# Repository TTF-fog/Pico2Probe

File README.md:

# a RP2354-based debugprobe

An updated version of the original [debugprobe](https://www.raspberrypi.com/documentation/microcontrollers/debug-probe.html) with the following changes - 
- Based on the RP2354A
- USB-C (i just really hate micro-b)
- a configurable addressable RGB led

### Build

SWD, uart works

# Why did i make this?

1. Does one need to justify the act of creation? (or, in other words, why not?) (please do not take that out of context)
2. I had no way of debugging except plain UART (which is annoying), so i wanted something that would let me use an actual debugger
3. Wanted to make something using the RP2354A

# Setting Up
1. the board will already have a bootloader on it, plug it in and mount the drive
2. do git submodule sync and git submodule update --init --recursive
3. cd into debugprobe directory and
4. cmake -B build-pico2probe -DPICO_BOARD=pico2probe && make -C build-pico2probe -j$(nproc)
5. drag the pico2probe.uf2 file into the flash drive

# Firmware Modifications
- opening and closing the port at 1200 baud automatically puts the device into BOOTSEL mode
- board support files for the pico2probe
# Usage
for UART RX/TX, 
```shell
screen /dev/ttyACMx
```
for using SWD, eg. flashing a rp2040 do:
```shell
sudo openocd -f interface/cmsis-dap.cfg -f target/rp2040.cfg -c "adapter speed 5000" -c "program blink.elf verify reset exit"
```
# (Sub)Links
- [BOM](PCB/production_files/BOM.csv)
- [Design Files](PCB/Design%20Files/)
- [Schematic PDF](PCB/Design%20Files/schem.pdf/Pico2Probe.pdf)
- [Zine](zine.pdf)
- [Gerbers](PCB/production_files/GERBER-Pico2Probe.zip)

# Images

# Current Issues
- Silkscreen text is difficult to read due to small size
- buffer on UART is on wrong pin
- uses green and red leds, not yellow and red leds
- solder jumpers are difficult to use reliably
- bootsel does not work due to resistor configuuration issues

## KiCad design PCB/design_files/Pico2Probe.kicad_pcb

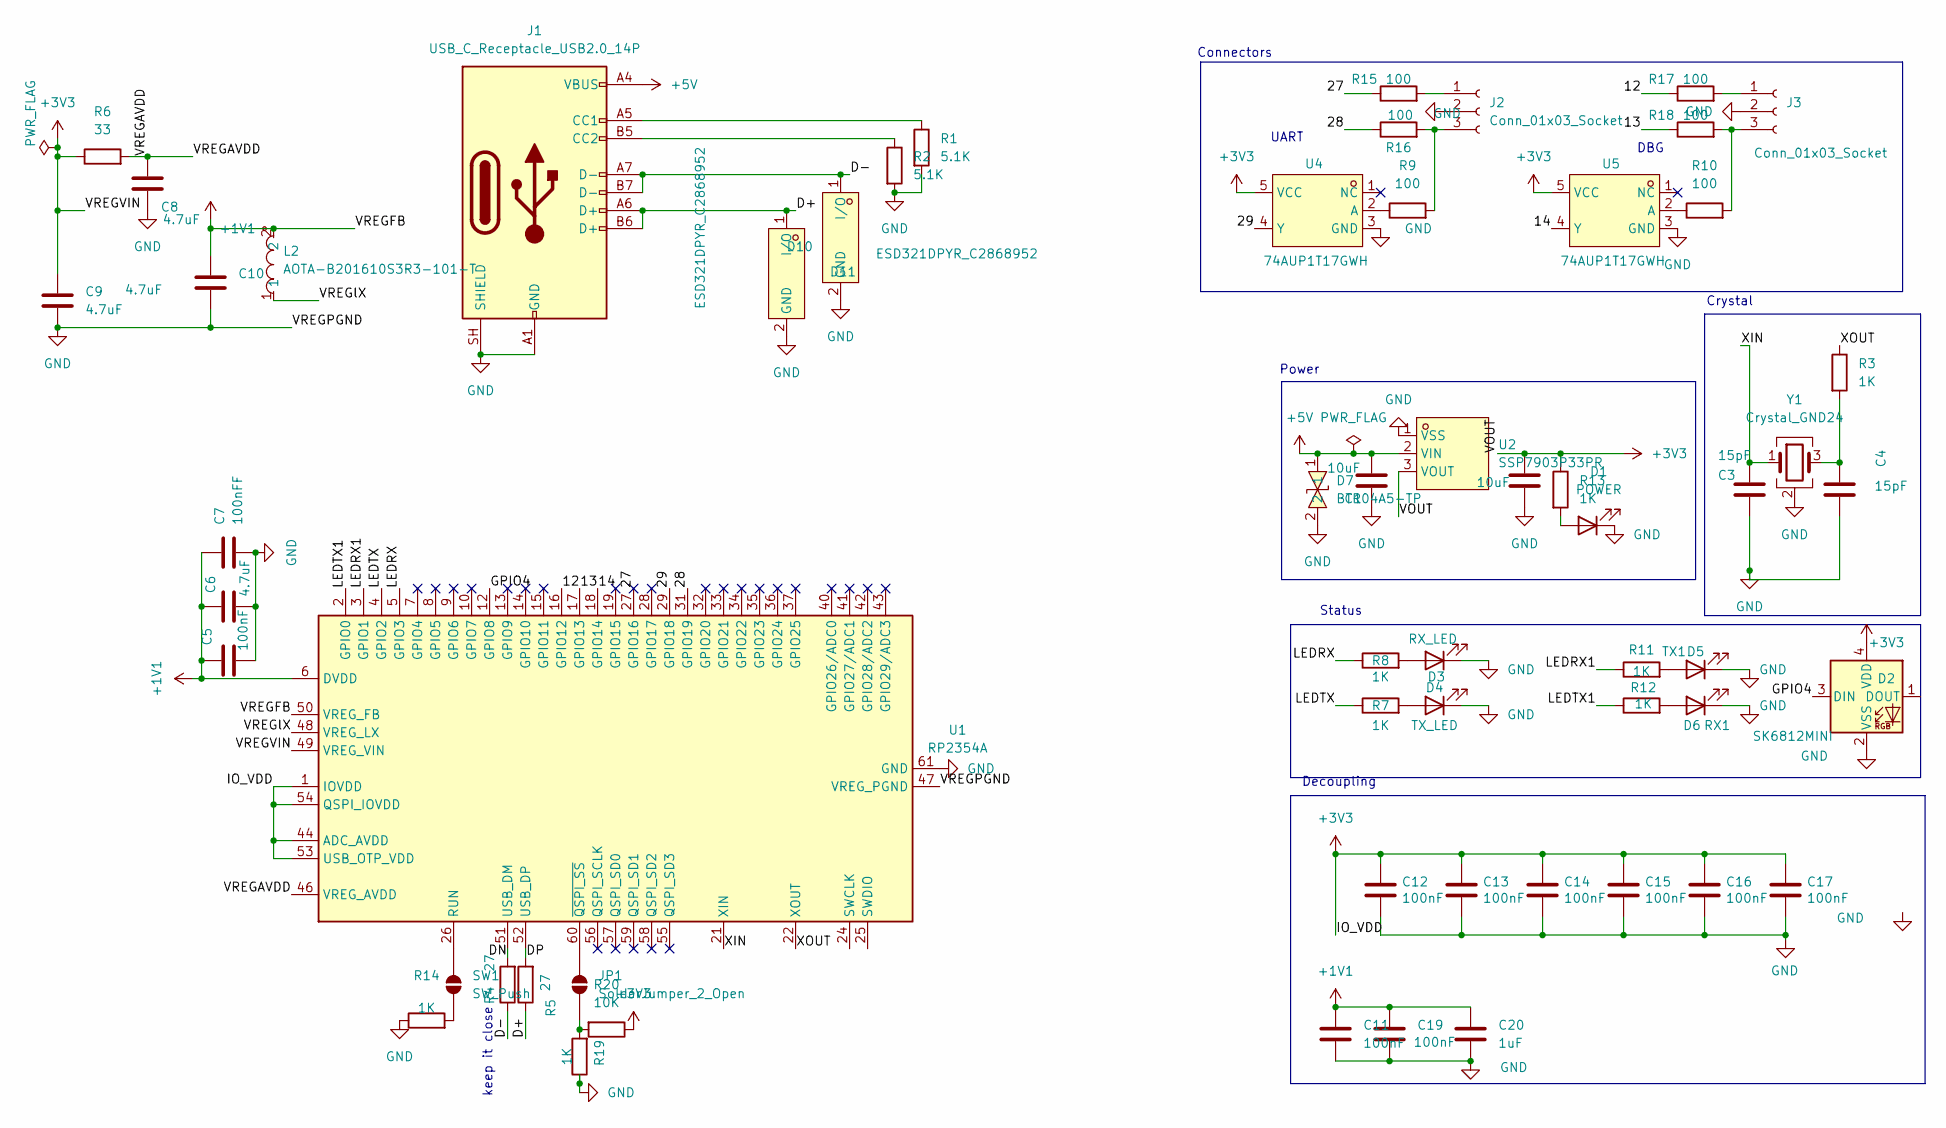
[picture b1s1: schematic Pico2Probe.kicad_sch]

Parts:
C1, C2: 10uF; C_0402_1005Metric
C3, C4: 15pF; C_0402_1005Metric
C5, C11, C12, C13, C14, C15, C16, C17, C19: 100nF; C_0402_1005Metric
C6, C8, C9, C10: 4.7uF; C_0402_1005Metric
C7: 100nFF; C_0402_1005Metric
C20: 1uF; C_0402_1005Metric
D1: POWER; LED_0402_1005Metric
D2: SK6812MINI; LED_SK6812_EC15_1.5x1.5mm
D3: RX_LED; LED_0402_1005Metric
D4: TX_LED; LED_0402_1005Metric
D5: TX1; LED_0402_1005Metric
D6: RX1; LED_0402_1005Metric
D7: BTR04A5-TP; D0402-BI; MPN BTR04A5-TP; LCSC Part C42406343
D10, D11: ESD321DPYR_C2868952; X1SON-2_L1.0-W0.6-P0.65-RD-1; MPN ESD321DPYR; LCSC Part C2868952
J1: USB_C_Receptacle_USB2.0_14P; USB_C_Receptacle_HRO_TYPE-C-31-M-12
J2, J3: Conn_01x03_Socket; JST_SH_BM03B-SRSS-TB_1x03-1MP_P1.00mm_Vertical
JP1: SolderJumper_2_Open; SolderJumper-2_P1.3mm_Open_RoundedPad1.0x1.5mm
L2: AOTA-B201610S3R3-101-T; IND-SMD_L2.0-W1.6_AOTA-B201610S3R3-101-T; MPN AOTA-B201610S3R3-101-T; LCSC Part C42411119
R1, R2: 5.1K; R_0402_1005Metric
R3, R7, R8, R11, R12, R13, R14, R19: 1K; R_0402_1005Metric
R4, R5: 27; R_0402_1005Metric
R6: 33; R_0402_1005Metric
R9, R10, R15, R16, R17, R18: 100; R_0402_1005Metric
R20: 10K; R_0402_1005Metric
SW1: SW_Push; SolderJumper-2_P1.3mm_Open_RoundedPad1.0x1.5mm
U1: RP2354A; QFN-60-1EP_7x7mm_P0.4mm_EP3.4x3.4mm
U2: SSP7903P33PR; SOT-89-3_L4.5-W2.5-P1.50-LS4.1-BR; MPN SSP7903P33PR; LCSC Part C2965586
U4, U5: 74AUP1T17GWH; TSSOP-5_L2.1-W1.3-P0.65-LS2.2-BR; MPN 74AUP1T17GWH
Y1: Crystal_GND24; Crystal_SMD_3225-4Pin_3.2x2.5mm

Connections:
+1V1: C5.1, C6.1, C7.1, C10.1, C11.1, C19.1, C20.1, L2.2, U1.6 (DVDD), U1.23 (DVDD), U1.39 (DVDD), U1.50 (VREG_FB)
+3V3: C2.1, C9.1, C12.1, C13.1, C14.1, C15.1, C16.1, C17.1, D2.4 (VDD), R6.1, R13.1, R20.1, U1.1 (IOVDD), U1.11 (IOVDD), U1.20 (IOVDD), U1.30 (IOVDD), U1.38 (IOVDD), U1.44 (ADC_AVDD), U1.45 (IOVDD), U1.49 (VREG_VIN), U1.53 (USB_OTP_VDD), U1.54 (QSPI_IOVDD), U2.3 (VOUT), U4.5 (VCC), U5.5 (VCC)
+5V: C1.1, D7.1, J1.A4 (VBUS), J1.A9 (VBUS), J1.B4 (VBUS), J1.B9 (VBUS), U2.2 (VIN)
/12: R17.1, U1.16 (GPIO12)
/13: R18.1, U1.17 (GPIO13)
/14: U1.18 (GPIO14), U5.4 (Y)
/27: R15.1, U1.27 (GPIO16)
/28: R16.1, U1.31 (GPIO19)
/29: U1.29 (GPIO18), U4.4 (Y)
/D+: D11.1 (I/O), J1.A6 (D+), J1.B6 (D+), R5.1
/D-: D10.1 (I/O), J1.A7 (D-), J1.B7 (D-), R4.1
/DN: R4.2, U1.51 (USB_DM)
/DP: R5.2, U1.52 (USB_DP)
/GPIO4: D2.3 (DIN), U1.12 (GPIO8)
/LEDRX: R8.1, U1.5 (GPIO3)
/LEDRX1: R11.1, U1.3 (GPIO1)
/LEDTX: R7.1, U1.4 (GPIO2)
/LEDTX1: R12.1, U1.2 (GPIO0)
/VREGAVDD: C8.1, R6.2, U1.46 (VREG_AVDD)
/VREGlX: L2.1, U1.48 (VREG_LX)
/XIN: C3.1, U1.21 (XIN), Y1.1
/XOUT: R3.1, U1.22 (XOUT)
GND: C1.2, C2.2, C3.2, C4.2, C5.2, C6.2, C7.2, C8.2, C9.2, C10.2, C11.2, C12.2, C13.2, C14.2, C15.2, C16.2, C17.2, C19.2, C20.2, D1.1 (K), D2.2 (VSS), D3.1 (K), D4.1 (K), D5.1 (K), D6.1 (K), D7.2, D10.2 (GND), D11.2 (GND), J1.A1 (GND), J1.A12 (GND), J1.B1 (GND), J1.B12 (GND), J1.SH (SHIELD), J2.2, J3.2, R1.2, R2.2, R14.1, R19.1, U1.47 (VREG_PGND), U1.61 (GND), U2.1 (VSS), U4.3 (GND), U5.3 (GND), Y1.2 (G), Y1.4 (G); also elsewhere on the board
unnamed: C4.1, R3.2, Y1.3
unnamed 24: D1.2 (A), R13.2; also elsewhere on the board
unnamed: D3.2 (A), R8.2
unnamed: D4.2 (A), R7.2
unnamed: D5.2 (A), R11.2
unnamed: D6.2 (A), R12.2
unnamed: J1.A5 (CC1), R1.1
unnamed: J1.B5 (CC2), R2.1
unnamed: J2.1, R15.2
unnamed: J2.3, R9.2, R16.2
unnamed: J3.1, R17.2
unnamed: J3.3, R10.2, R18.2
unnamed: JP1.1 (A), R19.2, R20.2
unnamed: JP1.2 (B), U1.60 (~QSPI_SS)
unnamed: R14.2, SW1.1 (A)
unnamed: SW1.2 (B), U1.26 (RUN)
unnamed: R9.1, U4.2 (A)
unnamed: R10.1, U5.2 (A)

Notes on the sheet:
UART
keep it close
Connectors
Crystal
Decoupling
DBG
Status
Power

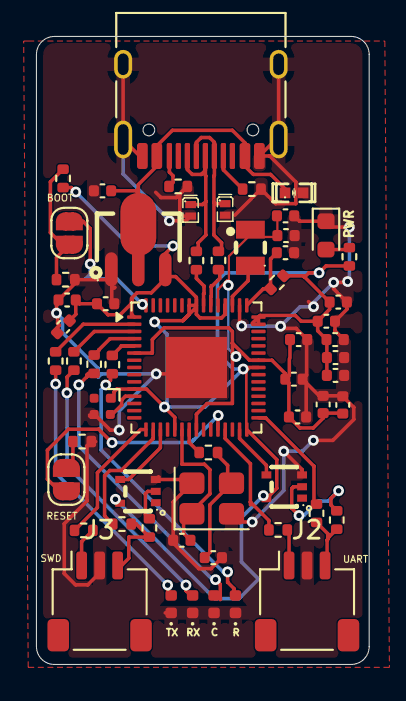
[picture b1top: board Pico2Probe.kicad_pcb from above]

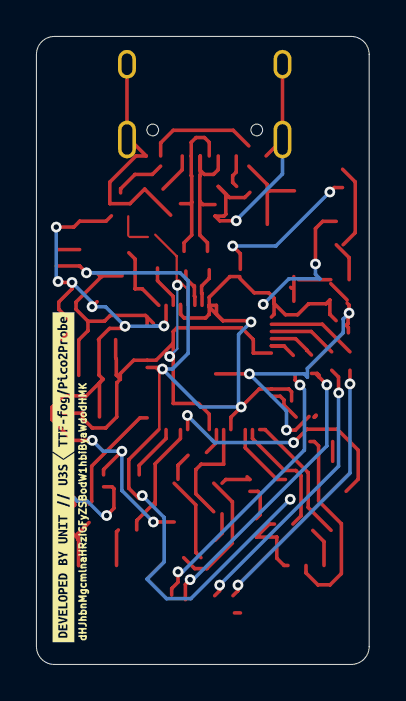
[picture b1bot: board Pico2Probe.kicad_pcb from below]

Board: 2 copper layers, 18.5 x 34.9 mm, 61 parts (2 on the bottom side), 41 nets.

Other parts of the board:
PWR: POWER; LED_0603_1608Metric
kibuzzard-6A06DE47: G***; kibuzzard-6A06DE47
kibuzzard-6A06DEAD: G***; kibuzzard-6A06DEAD

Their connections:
GND: PWR.1 (K); also elsewhere on the board
unnamed 24: PWR.2 (A); also elsewhere on the board

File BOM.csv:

Comment,Designator,Footprint,LCSC,Quantity,LCSC_Link,Original Cost,LCSC Unit Price (USD),BOM Qty Cost (USD),MOQ,MOQ Order Qty,MOQ Order Cost (USD),Stock/Pricing Status,Source URL
100,"R10,R15,R16,R17,R18,R9",R_0402_1005Metric,C25076,6,https://lcsc.com/product/C25076.html,$0.03,0.001,0.006,100,100,0.1,In stock,https://www.lcsc.com/product-detail/C25076.html
100nF,"C11,C12,C13,C14,C15,C16,C17,C19,C5",C_0402_1005Metric,C1525,9,https://lcsc.com/product/C1525.html,$0.08,0.0015,0.0135,100,100,0.15,In stock,https://www.lcsc.com/product-detail/C1525.html
100nFF,C7,C_0402_1005Metric,C1525,1,https://lcsc.com/product/C1525.html,$0.13,0.0015,0.0015,100,100,0.15,In stock,https://www.lcsc.com/product-detail/C1525.html
10uF,"C1,C2",C_0402_1005Metric,C15525,2,https://lcsc.com/product/C15525.html,$0.07,0.007,0.014,100,100,0.7,In stock,https://www.lcsc.com/product-detail/C15525.html
15pF,"C3,C4",C_0402_1005Metric,C1548,2,https://lcsc.com/product/C1548.html,,0.0012,0.0024,100,100,0.12,In stock,https://www.lcsc.com/product-detail/C1548.html
1K,"R11,R12,R13,R14,R19,R3,R7,R8",R_0402_1005Metric,C11702,8,https://lcsc.com/product/C11702.html,,0.0011,0.0088,100,100,0.11,Out of stock,https://www.lcsc.com/product-detail/C11702.html
1uF,C20,C_0402_1005Metric,C52923,1,https://lcsc.com/product/C52923.html,,0.004,0.004,100,100,0.4,In stock,https://www.lcsc.com/product-detail/C52923.html
27,"R4,R5",R_0402_1005Metric,C138021,2,https://lcsc.com/product/C138021.html,,0.0008,0.0016,100,100,0.08,In stock,https://www.lcsc.com/product-detail/C138021.html
3.3u,L1,L_0402_1005Metric,C48946153,1,https://lcsc.com/product/C48946153.html,,0.0425,0.0425,10,10,0.425,In stock,https://www.lcsc.com/product-image/C48946153.html
33,R6,R_0402_1005Metric,C25105,1,https://lcsc.com/product/C25105.html,,0.0009,0.0009,100,100,0.09,In stock,https://www.lcsc.com/product-detail/C25105.html
4.7uF,"C10,C6,C8,C9",C_0402_1005Metric,C23733,4,https://lcsc.com/product/C23733.html,,0.0063,0.0252,50,50,0.315,In stock,https://www.lcsc.com/product-detail/C23733.html
5.1K,"R1,R2",R_0402_1005Metric,C25905,2,https://lcsc.com/product/C25905.html,,0.0009,0.0018,100,100,0.09,In stock,https://www.lcsc.com/product-detail/C25905.html
BTR04A5-TP,D7,D0402-BI,C42406343,1,https://lcsc.com/product/C42406343.html,,0.0252,0.0252,20,20,0.504,In stock,https://www.lcsc.com/product-detail/C42406343.html
Conn_01x03_Socket,"J2,J3",JST_ACH_BM03B-ACHSS-GAN-ETF_1x03-1MP_P1.20mm_Vertical,C53368148,2,https://lcsc.com/product/C53368148.html,,,,1,1,0.38,In stock,https://www.lcsc.com/product-detail/C53368148.html
Crystal_GND24,Y1,Crystal_SMD_3225-4Pin_3.2x2.5mm,C20625731,1,https://lcsc.com/product/C20625731.html,,0.2947,0.2947,5,5,1.4735,In stock,https://www.lcsc.com/product-detail/C20625731.html
ESD321DPYR_C2868952,"D10,D11",X1SON-2_L1.0-W0.6-P0.65-RD-1,C2868952,2,https://lcsc.com/product/C2868952.html,1.81,0.2751,0.5502,5,5,1.3755,In stock,https://www.lcsc.com/product-detail/C2868952.html
RP2354A,U1,QFN-60-1EP_7x7mm_P0.4mm_EP3.4x3.4mm,C41378174,1,https://lcsc.com/product/C41378174.html,3,1.4926,1.4926,1,1,1.4926,Out of stock,https://www.lcsc.com/product-detail/C41378174.html
RX1,D6,LED_0402_1005Metric,C598352,1,https://lcsc.com/product/C598352.html,0.447,0.3451,0.3451,1,1,0.3451,In stock,https://www.lcsc.com/product-detail/C598352.html
RX_LED,D3,LED_0402_1005Metric,C598352,1,https://lcsc.com/product/C598352.html,0.447,0.3451,0.3451,1,1,0.3451,In stock,https://www.lcsc.com/product-detail/C598352.html
TX1,D5,LED_0402_1005Metric,C598352,1,https://lcsc.com/product/C598352.html,0.447,0.3451,0.3451,1,1,0.3451,In stock,https://www.lcsc.com/product-detail/C598352.html
TX_LED,D4,LED_0402_1005Metric,C598352,1,https://lcsc.com/product/C598352.html,0.447,0.3451,0.3451,1,1,0.3451,In stock,https://www.lcsc.com/product-detail/C598352.html
USB_C_Receptacle_USB2.0_14P,J1,USB_C_Receptacle_HRO_TYPE-C-31-M-12,C165948,1,https://lcsc.com/product/C165948.html,,0.1709,0.1709,5,5,0.8545,In stock,https://www.lcsc.com/product-detail/C165948.html
MCP1700x-330xxMB,U6,SOT-89-3,C511277,1,https://lcsc.com/product/C511277,0.8,0.803,0.803,1,1,0.803,In stock,https://www.lcsc.com/product-detail/C511277.html
POWER,D1,LED_0402_1005Metric,C598352,1,https://lcsc.com/product/C598352.html,,0.3451,0.3451,1,1,0.3451,In stock,https://www.lcsc.com/product-detail/C598352.html
74AUP1T17GWH,U4,TSSOP-5_L2.1-W1.3-P0.65-LS2.2-BR,C545951,1,https://lcsc.com/product/C545951.html,$2.72,0.2797,0.2797,5,5,1.3985,In stock,https://www.lcsc.com/product-detail/C545951.html
SK6812MINI,D2,LED_SK6812_EC15_1.5x1.5mm,C2890035,1,https://lcsc.com/product/C2890035.html,,0.093,0.093,5,5,0.465,In stock,https://www.lcsc.com/product-detail/C2890035.html
74AUP1T17GWH,U5,TSSOP-5_L2.1-W1.3-P0.65-LS2.2-BR,C545951,1,https://lcsc.com/product/C545951.html,$2.72,0.2797,0.2797,5,5,1.3985,In stock,https://www.lcsc.com/product-detail/C545951.html
,,,,,,,Totals,5.8367,,,14.6006,,

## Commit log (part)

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2026-05-14 pcb 1
2026-05-17 update organization + pcb
2026-05-17 add the funny submodule
2026-05-17 imrpvoe readme
2026-05-17 the zine is a WIP pls dont kill me
2026-05-17 idk bro anymore
2026-05-17 minor formatting changes
2026-05-18 add new BoM with costs
2026-05-18 fijh
